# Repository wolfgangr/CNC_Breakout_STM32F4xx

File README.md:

## My Plan: build a Breakout Board for Blackpills

- [grbl-HAL STM32F4xx for blackpill_alt2 layout](https://github.com/grblHAL/STM32F4xx/blob/master/boards/blackpill_alt2_map.h)
- open collector drivers for all outputs
- screw connectors for high power stepper drivers and pins for smaller formats
- optocouplers for inputs
- control LED (optionally jumpered) for all in- and outputs
- jumpers on all Blackpill connectors, so that each pin can be rerouted independently
- 4 axes
- options for spindle encoders, VFD driver, THC analog input...
- wide input voltage range
- manufactured by JCBPCB or similiar

current projects in mind:
- routers/mills with auto-squared Y-axis
- lathe with spindle index for thread cutting
- plasma cutter with auto-squared Y-axis and torch height control

I selectet to fork Terje Io's project because of the kicad file format.

In the end, most of the hardware was closer to
https://github.com/phil-barrett/grblHAL-teensy-4.x
- simply because this design was closer to what I had in mind.

Please find updated information and discussion here at the github/grbl-HAL/core discussion area:
[STM324X1 blackpill experimental versatile GRBL-breakout board](https://github.com/grblHAL/core/discussions/562)

Project state as of July 2024:
- first batch arrived from the fab
- still yet untested

CAVEAT - DISCLAIMER:
Don't expect anything serious from the ideas, concepts and files delivered here.
Expect the worst, like your house set under fire, your machine going bust or whatever evil you may think of.

======== End of fork remarks ===========

## CNC Breakout board for Nucleo-64 based development boards using ST morpho extension header

[grblHAL driver](https://github.com/grblHAL/STM32F4xx) support for [Nucleo F411RE](https://www.st.com/en/evaluation-tools/nucleo-f411re.html) and [Nucleo F446RE](https://www.st.com/en/evaluation-tools/nucleo-f446re.html) development boards.

**NOTE:** design files are in [KiCad 5](http://www.kicad.org/) format!

**Features:**

* Four layer board

* 4-axis motor support with separate enable for all axes.

* On-board sockets for Polulu \(A4998 and DRV8825\) or Trinamic \(TMC2130 or TMC5160 - SPI mode, TMC2209 - UART mode\) style motor driver modules.

* Opto-coupled limit and signal inputs (X, Y, Z, A, Probe, Reset/E-Stop, Door, Feed Hold and Cycle Start).

* Opto-coupled signal outputs \(Spindle on, Spindle direction, Flood, Mist, Aux0 and Aux1\).
Outputs are open drain \(ULN2003\) capable of draining 500mA, enough to drive most relays directly.

* Jumper selectable drive voltage for inputs and outputs, either 5V internally supplied or 5-30V externally supplied. 
If externally supplied inputs and outputs can be made galvanically isolated from the controller via jumper settings.

* 5V buffered PWM output for spindle speed control.

* Optional optocoupled DC spindle output, can be made galvanically isolated via jumper setting. External supply voltage limited to rating of filtering capacitor C7 (max. 30V).

* I2C port with jumper selectable drive voltage \(3.3V or 5V\). This is complemented with a 5V tolerant input pin that may be used as an interrupt source, eg. for the strobe signal from a I2C-based keypad.

* Two GPIO ports, with two pins each. One is unbuffered and can be used for serial communincation, eg. for MPG or VFD control. One is input only and has 5V tolerant pins.

* Optional on-board EEPROM/FRAM for persistent storage of settings.

* SPI based SD-card interface. If not in use some or all pins may be used as GPIO or as a generic SPI interface with one chip select line, depending on motor drivers used.

---

I have a number of _bare_ boards available:

* 1.0 \(preliminary version\): 7 pcs. These do not support Trinamic drivers in SPI/UART mode and has a couple of correctable routing errors in the spindle PWM -> spindle DC circuit. Price: shipping at cost.

* 1.0b: 2 pcs. Price: EUR 5/pcs + shipping at cost. These are missing a pullup resistor for the keypad strobe input - this _may_ affect operation of the keypad plugin. Easy to add externally.

These boards are gold plated \(ENIG finish\).

* 1.0c: \(current version\) Not yet available.

I do not plan to offer populated boards as either I have to solder them myself \(will be expensive\) or place an order for ready made boards \(with only SMD components soldered\).  
A redesign is likely required for ready made boards as some of the components may not be available from the standard selection offered by e.g. [JLPCB](https://jlcpcb.com/).

It would be great if someone would get populated boards made and offered for sale as I am currently not prepared to do that.

---

2021-08-22

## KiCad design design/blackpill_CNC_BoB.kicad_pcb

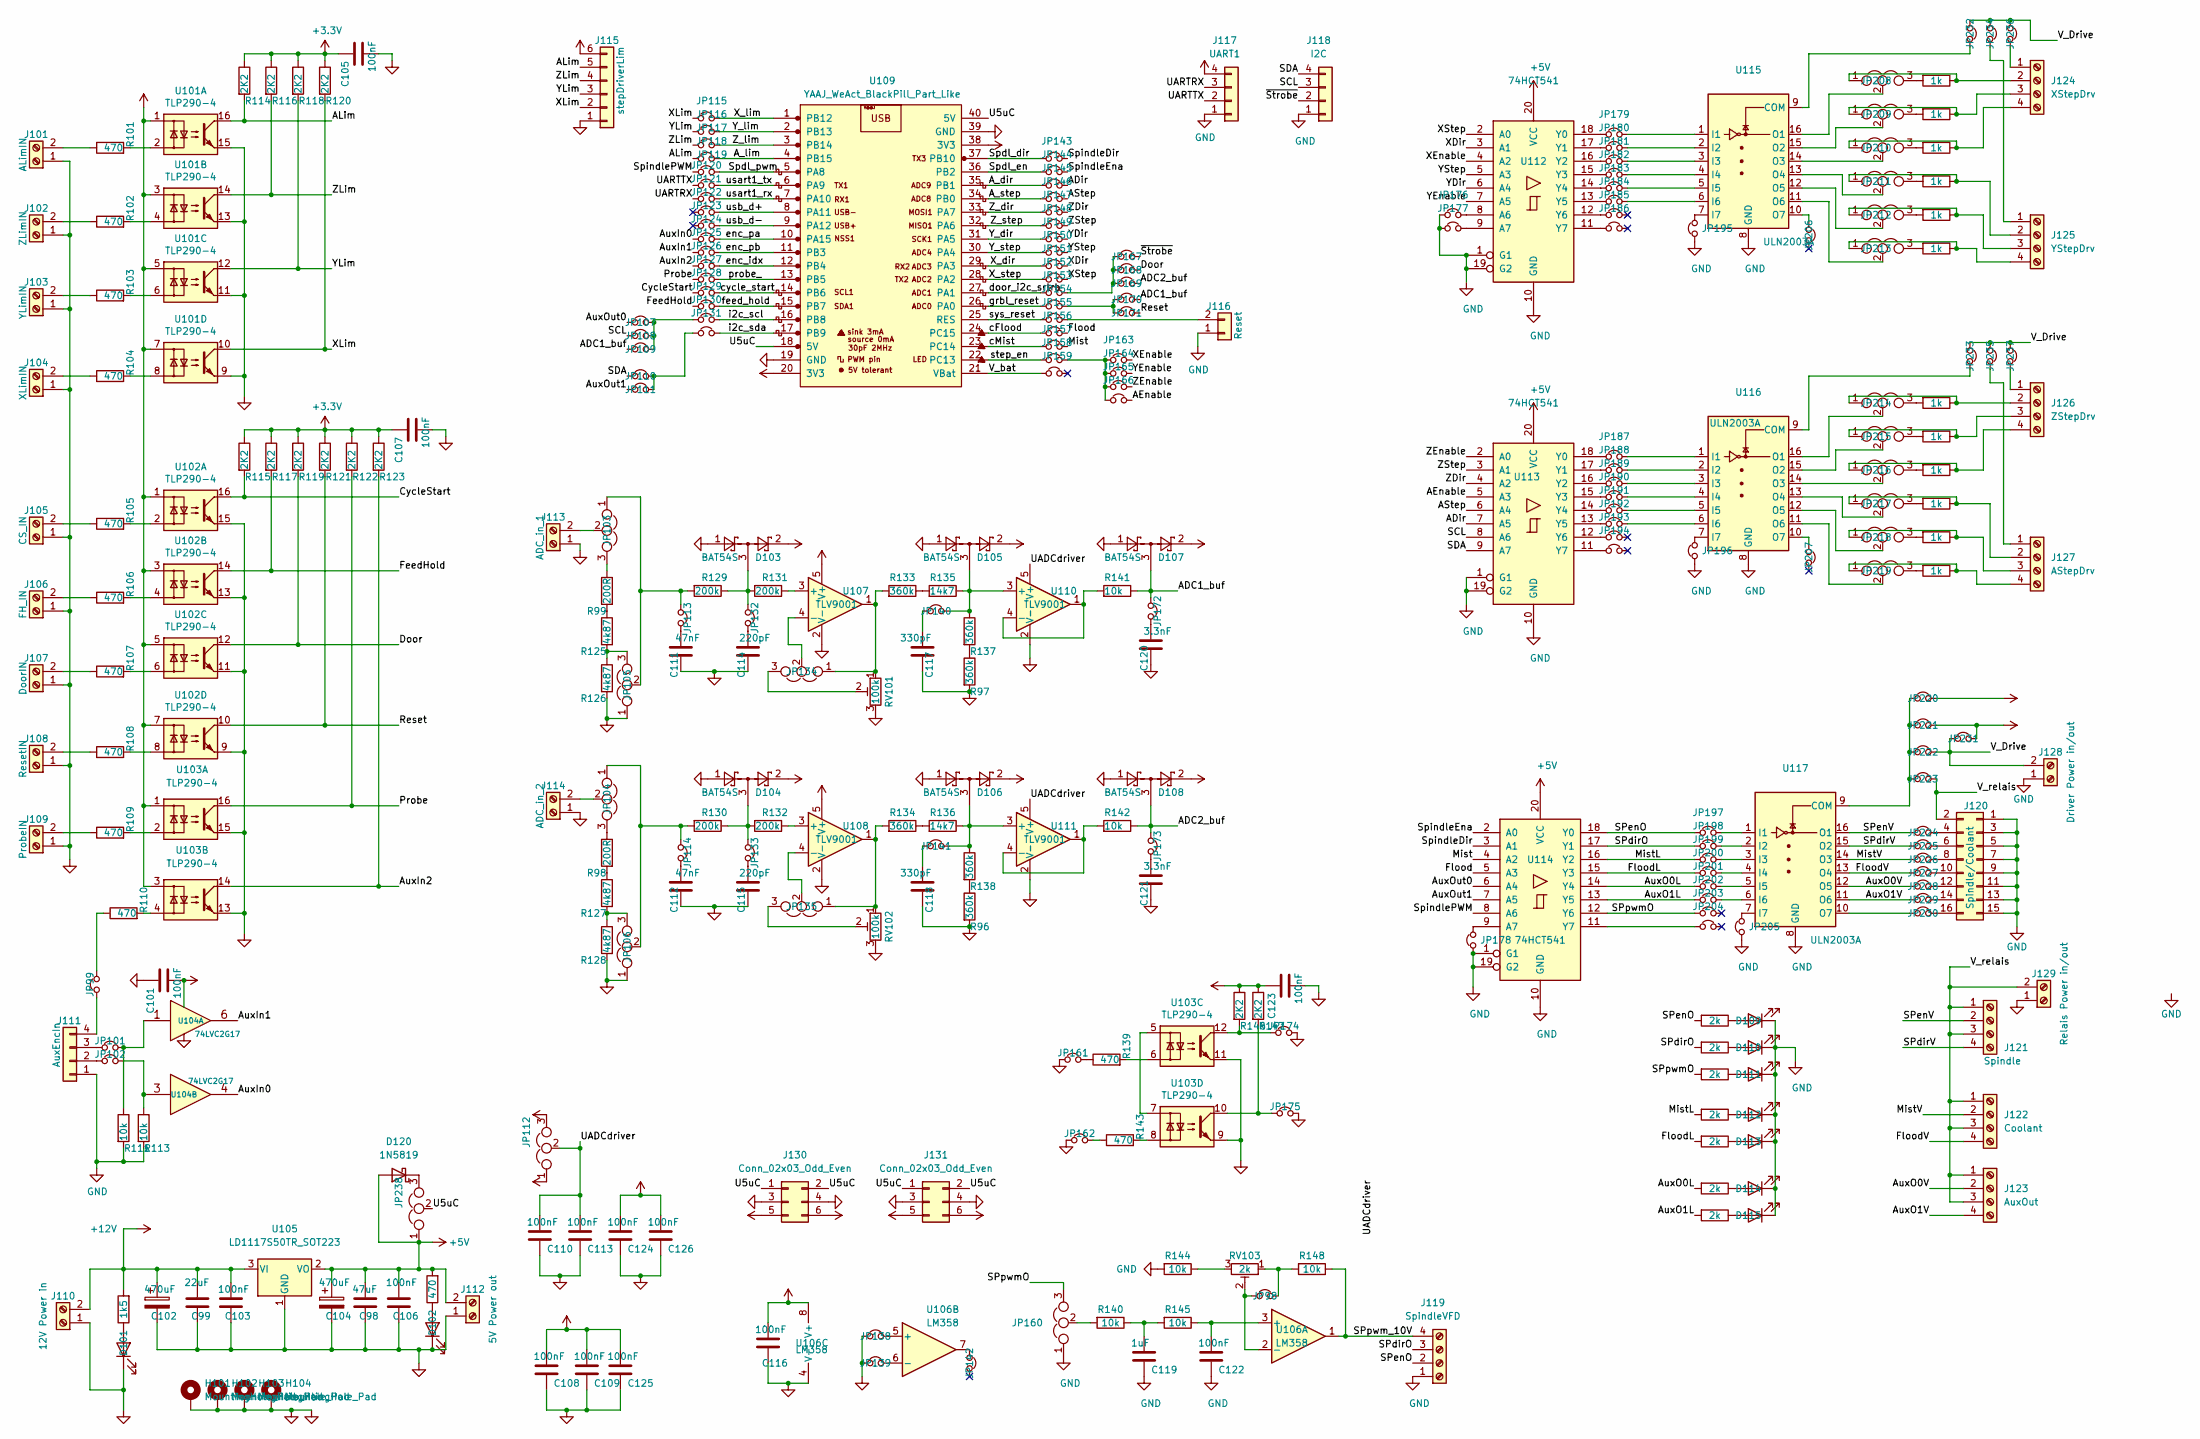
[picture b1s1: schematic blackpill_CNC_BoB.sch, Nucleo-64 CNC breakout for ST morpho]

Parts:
C98: 47uF; C_1206_3216Metric
C99: 22uF; C_1206_3216Metric
C101, C103, C105, C106, C107, C108, C109, C110, C113, C116, C122, C123, C124, C125, C126: 100nF; C_0603_1608Metric
C102, C104: 470uF; CP_Elec_10x10
C111, C112: 47nF; C_0603_1608Metric
C114, C115: 220pF; C_0402_1005Metric
C117, C118: 330pF; C_0603_1608Metric
C119: 1uF; C_0603_1608Metric
C120, C121: 3.3nF; C_0603_1608Metric
D101, D102: LED; LED_0805_2012Metric
D103, D104, D105, D106, D107, D108: BAT54S; SOT-23
D109, D110, D111, D112, D113, D114, D115: LED; LED_0603_1608Metric
D120: 1N5819; D_SOD-323
H101, H102, H103, H104: MountingHole_Pad; MountingHole_3.2mm_M3_Pad
J101: ALimIN; ScrewTerminal_1x2_P2.54mm_Vertical
J102: ZLimIN; ScrewTerminal_1x2_P2.54mm_Vertical
J103: YLimIN; ScrewTerminal_1x2_P2.54mm_Vertical
J104: XLimIN; ScrewTerminal_1x2_P2.54mm_Vertical
J105: CS_IN; ScrewTerminal_1x2_P2.54mm_Vertical
J106: FH_IN; ScrewTerminal_1x2_P2.54mm_Vertical
J107: DoorIN; ScrewTerminal_1x2_P2.54mm_Vertical
J108: ResetIN; ScrewTerminal_1x2_P2.54mm_Vertical
J109: ProbeIN; ScrewTerminal_1x2_P2.54mm_Vertical
J110: 12V Power in; PhoenixContact_MSTBA_2,5_2-G-5,08_1x02_P5.08mm_Horizontal
J111: AuxEncIn; PinSocket_1x04_P2.54mm_Vertical
J112: 5V Power out; ScrewTerminal_1x2_P2.54mm_Vertical
J113: ADC_in_1; ScrewTerminal_1x2_P2.54mm_Vertical
J114: ADC_in_2; ScrewTerminal_1x2_P2.54mm_Vertical
J115: stepDriverLim; PinSocket_1x06_P2.54mm_Vertical
J116: Reset; PinSocket_1x02_P2.54mm_Vertical
J117: UART1; PinSocket_1x04_P2.54mm_Vertical
J118: I2C; PinSocket_1x04_P2.54mm_Vertical
J119: SpindleVFD; ScrewTerminal_1x4_P2.54mm_Vertical
J120: Spindle/Coolant; PinSocket_2x08_P2.54mm_Vertical
J121: Spindle; ScrewTerminal_1x4_P2.54mm_Vertical
J122: Coolant; ScrewTerminal_1x4_P2.54mm_Vertical
J123: AuxOut; ScrewTerminal_1x4_P2.54mm_Vertical
J124: XStepDrv; ScrewTerminal_1x4_P2.54mm_Vertical
J125: YStepDrv; ScrewTerminal_1x4_P2.54mm_Vertical
J126: ZStepDrv; ScrewTerminal_1x4_P2.54mm_Vertical
J127: AStepDrv; ScrewTerminal_1x4_P2.54mm_Vertical
J128: Driver Power in/out; ScrewTerminal_1x2_P2.54mm_Vertical
J129: Relais Power in/out; ScrewTerminal_1x2_P2.54mm_Vertical
J130, J131: Conn_02x03_Odd_Even; PinHeader_2x03_P2.54mm_Vertical
JP98, JP99, JP101, JP102, JP107, JP108, JP109, JP110, JP111, JP113, JP114, JP115, JP116, JP117, JP118, JP119, JP120, JP121, JP122, JP123, JP124, JP125, JP126, JP127, JP128, JP129, JP130, JP131, JP132, JP133, JP138, JP139, JP140, JP141, JP142, JP143, JP144, JP145, JP146, JP147, JP148, JP149, JP150, JP151, JP152, JP153, JP154, JP155, JP156, JP157, JP158, JP159, JP161, JP162, JP163, JP164, JP165, JP166, JP167, JP168, JP169, JP170, JP171, JP172, JP173, JP174, JP175, JP176, JP177, JP178, JP179, JP180, JP181, JP182, JP183, JP184, JP185, JP186, JP187, JP188, JP189, JP190, JP191, JP192, JP193, JP194, JP195, JP196, JP197, JP198, JP199, JP200, JP201, JP202, JP203, JP204, JP205, JP206, JP207, JP220, JP221, JP222, JP223, JP224, JP225, JP226, JP227, JP228, JP229, JP230, JP231, JP232, JP233, JP234, JP235, JP236, JP237: Jumper_NC_Small; PinHeader_1x02_P2.54mm_Vertical
JP103, JP104, JP105, JP106, JP112, JP134, JP135, JP160, JP208, JP209, JP210, JP211, JP212, JP213, JP214, JP215, JP216, JP217, JP218, JP219, JP238: Jumper_NC_Dual; PinHeader_1x03_P2.54mm_Vertical
R96, R97, R133, R134, R137, R138: 360k; R_0603_1608Metric
R98, R99: 200R; R_0603_1608Metric
R101, R102, R103, R104, R105, R106, R107, R108, R109, R110, R124, R139, R143: 470; R_0805_2012Metric
R111, R113, R140, R141, R142, R144, R145, R148: 10k; R_0603_1608Metric
R112: 1k5; R_0805_2012Metric
R114, R115, R116, R117, R118, R119, R120, R121, R122, R123, R146, R147: 2K2; R_0603_1608Metric
R125, R126, R127, R128: 4k87; R_0805_2012Metric
R129, R130, R131, R132: 200k; R_0603_1608Metric
R135, R136: 14k7; R_0402_1005Metric
R149, R150, R151, R152, R153, R154, R167: 2k; R_0603_1608Metric
R155, R156, R157, R158, R159, R160, R161, R162, R163, R164, R165, R166: 1k; R_1206_3216Metric
RV101, RV102: 100k; Potentiometer_Bourns_3296W_Vertical
RV103: 2k; Potentiometer_Bourns_3296W_Vertical
U101, U102, U103: TLP290-4; SOP-16_4.4x10.4mm_P1.27mm
U104: 74LVC2G17; SOT-23-6
U105: LD1117S50TR_SOT223; SOT-223-3_TabPin2
U106: LM358; SOIC-8_3.9x4.9mm_P1.27mm
U107, U108, U110, U111: TLV9001; SOT-353_SC-70-5
U109: YAAJ_WeAct_BlackPill_Part_Like; YAAJ_WeAct_BlackPill_2
U112, U113, U114: 74HCT541; TSSOP-20_4.4x6.5mm_P0.65mm
U115, U116, U117: ULN2003A; SOIC-16_3.9x9.9mm_P1.27mm

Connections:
+5V: C98.1, C104.1, C106.1, C108.1, C109.1, C124.1, C125.1, C126.1, D103.2, D104.2, D120.2 (A), J112.2, J115.6, JP112.3, JP220.2, JP238.1, R124.2, U101.1, U101.3, U101.5, U101.7, U102.1, U102.3, U102.5, U102.7, U103.1, U103.3, U105.2 (VO), U107.5 (V+), U108.5 (V+), U112.20 (VCC), U113.20 (VCC), U114.20 (VCC)
+12V: C99.1, C102.1, C103.1, C116.1, J110.2, JP221.2, JP231.2, R112.2, U105.3 (VI), U106.8 (V+)
/ADC1_buf: D107.3, JP109.1, JP170.2, JP172.2, R141.1
/ADC2_buf: D108.3, JP169.2, JP173.2, R142.1
/ADir: JP145.2, U113.7 (A5)
/AEnable: JP166.2, U113.5 (A3)
/ALim: J115.5, JP118.1, R114.2, U101.16
/AStep: JP146.2, U113.6 (A4)
/A_dir: JP145.1, U109.35 (PB1)
/A_lim: JP118.2, U109.4 (PB15)
/A_step: JP146.1, U109.34 (PB0)
/AuxIn0: JP124.1, U104.4
/AuxIn1: JP125.1, U104.6
/AuxIn2: JP126.1, R123.2, U103.14
/AuxO0L: JP201.1, R154.2, U114.14 (Y4)
/AuxO0V: J123.2, JP228.1, U117.12 (O5)
/AuxO1L: JP202.1, R167.2, U114.13 (Y5)
/AuxO1V: J123.4, JP229.1, U117.11 (O6)
/AuxOut0: JP107.1, U114.6 (A4)
/AuxOut1: JP111.1, U114.7 (A5)
/CycleStart: JP128.1, R115.2, U102.16
/Door: JP168.2, R119.2, U102.12
/FeedHold: JP129.1, R117.2, U102.14
/Flood: JP156.2, U114.5 (A3)
/FloodL: JP200.1, R153.2, U114.15 (Y3)
/FloodV: J122.4, JP227.1, U117.13 (O4)
/Mist: JP157.2, U114.4 (A2)
/MistL: JP199.1, R152.2, U114.16 (Y2)
/MistV: J122.2, JP226.1, U117.14 (O3)
/Probe: JP127.1, R122.2, U103.16
/Reset: JP171.2, R121.2, U102.10
/SCL: J118.3, JP108.1, U113.8 (A6)
/SDA: J118.4, JP110.1, U113.9 (A7)
/SPdirO: J119.3, JP198.1, R150.2, U114.17 (Y1)
/SPdirV: J121.4, JP225.1, U117.15 (O2)
/SPenO: J119.2, JP197.1, R149.2, U114.18 (Y0)
/SPenV: J121.2, JP224.1, U117.16 (O1)
/SPpwmO: JP160.3, JP203.1, R151.2, U114.12 (Y6)
/SPpwm_10V: J119.4, R148.1, U106.1
/Spdl_dir: JP143.1, U109.37 (PB10)
/Spdl_en: JP144.1, U109.36 (PB2)
/Spdl_pwm: JP119.2, U109.5 (PA8)
/SpindleDir: JP143.2, U114.3 (A1)
/SpindleEna: JP144.2, U114.2 (A0)
/SpindlePWM: JP119.1, U114.8 (A6)
/U5uC: J130.1, J130.2, J131.1, J131.2, JP238.2, U109.18 (5V), U109.40 (5V)
/UADCdriver: C110.1, C113.1, JP112.2, U110.5 (V+), U111.5 (V+)
/UARTRX: J117.3, JP121.1
/UARTTX: J117.2, JP120.1
/V_Drive: J128.2, JP222.2, JP231.1, JP232.1, JP233.1, JP234.1, JP235.1, JP236.1, JP237.1
/V_bat: JP159.1, U109.21 (VBat)
/V_relais: J120.2, J121.1, J121.3, J122.1, J122.3, J123.1, J123.3, J129.2, JP223.2
/XDir: JP151.2, U112.3 (A1)
/XEnable: JP163.2, U112.4 (A2)
/XLim: J115.2, JP115.1, R120.2, U101.10
/XStep: JP152.2, U112.2 (A0)
/X_dir: JP151.1, U109.29 (PA3)
/X_lim: JP115.2, U109.1 (PB12)
/X_step: JP152.1, U109.28 (PA2)
/YDir: JP149.2, U112.6 (A4)
/YEnable: JP164.2, U112.7 (A5)
/YLim: J115.3, JP116.1, R118.2, U101.12
/YStep: JP150.2, U112.5 (A3)
/Y_dir: JP149.1, U109.31 (PA5)
/Y_lim: JP116.2, U109.2 (PB13)
/Y_step: JP150.1, U109.30 (PA4)
/ZDir: JP147.2, U113.4 (A2)
/ZEnable: JP165.2, U113.2 (A0)
/ZLim: J115.4, JP117.1, R116.2, U101.14
/ZStep: JP148.2, U113.3 (A1)
/Z_dir: JP147.1, U109.33 (PA7)
/Z_lim: JP117.2, U109.3 (PB14)
/Z_step: JP148.1, U109.32 (PA6)
/cFlood: JP156.1, U109.24 (PC15)
/cMist: JP157.1, U109.23 (PC14)
/cycle_start: JP128.2, U109.14 (PB6)
/door_i2c_srtrb: JP153.1, U109.27 (PA1)
/enc_idx: JP126.2, U109.12 (PB4)
/enc_pa: JP124.2, U109.10 (PA15)
/enc_pb: JP125.2, U109.11 (PB3)
/feed_hold: JP129.2, U109.15 (PB7)
/grbl_reset: JP154.1, U109.26 (PA0)
/i2c_scl: JP130.2, U109.16 (PB8)
/i2c_sda: JP131.2, U109.17 (PB9)
/probe_: JP127.2, U109.13 (PB5)
/step_en: JP158.1, U109.22 (PC13)
/sys_reset: JP155.1, U109.25 (RES)
/usart1_rx: JP121.2, U109.7 (PA10)
/usart1_tx: JP120.2, U109.6 (PA9)
/usb_d+: JP122.2, U109.8 (PA11)
/usb_d-: JP123.2, U109.9 (PA12)
/~Strobe: J118.2, JP167.2
GND: C98.2, C99.2, C101.2, C102.2, C103.2, C104.2, C105.1, C106.2, C107.1, C108.2, C109.2, C110.2, C111.2, C112.2, C113.2, C114.2, C115.2, C116.2, C117.2, C118.2, C119.2, C120.2, C121.2, C122.2, C123.1, C124.2, C125.2, C126.2, D101.1 (K), D102.1 (K), D103.1, D104.1, D105.1, D106.1, D107.1, D108.1, D109.1 (K), D110.1 (K), D111.1 (K), D112.1 (K), D113.1 (K), D114.1 (K), D115.1 (K), H101.1, H102.1, H103.1, H104.1, J101.1, J102.1, J103.1, J104.1, J105.1, J106.1, J107.1, J108.1, J109.1, J110.1, J111.1, J112.1, J113.1, J114.1, J115.1, J116.1, J117.1, J118.1, J119.1, J120.1, J120.3, J120.5, J120.7, J120.9, J120.11, J120.13, J120.15, J128.1, J129.1, J130.3, J130.4, J131.3, J131.4, JP105.1, JP106.1, JP138.1, JP139.1, JP160.1, JP161.2, JP162.2, JP174.1, JP175.1, JP176.1, JP177.1, JP178.1, JP195.1, JP196.1, JP205.1, R96.2, R97.2, R111.2, R113.2, R126.2, R128.2, R144.2, RV101.3, RV102.3, U101.9, U101.11, U101.13, U101.15, U102.9, U102.11, U102.13, U102.15, U103.9, U103.11, U103.13, U103.15, U104.2 (GND), U105.1 (GND), U106.4 (V-), U107.2 (V-), U108.2 (V-), U109.19 (GND), U109.39 (GND), U110.2 (V-), U111.2 (V-), U112.1 (G1), U112.10 (GND), U112.19 (G2), U113.1 (G1), U113.10 (GND), U113.19 (G2), U114.1 (G1), U114.10 (GND), U114.19 (G2), U115.8 (GND), U116.8 (GND), U117.8 (GND)
unnamed: C111.1, JP113.1
unnamed: C112.1, JP114.1
unnamed: C114.1, JP132.1
unnamed: C115.1, JP133.1
unnamed: C117.1, JP140.1
unnamed: C118.1, JP141.1
unnamed: C119.1, R140.1, R145.2
unnamed: C120.1, JP172.1
unnamed: C121.1, JP173.1
unnamed: C122.1, R145.1, U106.3 (+)
unnamed: D101.2 (A), R112.1
unnamed: D102.2 (A), R124.1
unnamed: D103.3, JP132.2, R129.1, R131.2
unnamed: D104.3, JP133.2, R130.1, R132.2
unnamed: D105.3, JP140.2, R135.1, R137.1, U110.3 (+)
unnamed: D106.3, JP141.2, R136.1, R138.1, U111.3 (+)
unnamed: D109.2 (A), R149.1
unnamed: D110.2 (A), R150.1
unnamed: D111.2 (A), R151.1
unnamed: D112.2 (A), R152.1
unnamed: D113.2 (A), R153.1
unnamed: D114.2 (A), R154.1
unnamed: D115.2 (A), R167.1
unnamed: D120.1 (K), JP238.3
unnamed: J101.2, R101.1
unnamed: J102.2, R102.1
unnamed: J103.2, R103.1
unnamed: J104.2, R104.1
unnamed: J105.2, R105.1
unnamed: J106.2, R106.1
unnamed: J107.2, R107.1
unnamed: J108.2, R108.1
unnamed: J109.2, R109.1
unnamed: J111.2, JP102.2
unnamed: J111.3, JP101.2
unnamed: J111.4, JP99.2
unnamed: J113.2, JP103.2
unnamed: J114.2, JP104.2
unnamed: J116.2, JP155.2
unnamed: J120.4, JP224.2
unnamed: J120.6, JP225.2
unnamed: J120.8, JP226.2
unnamed: J120.10, JP227.2
unnamed: J120.12, JP228.2
unnamed: J120.14, JP229.2
unnamed: J120.16, JP230.2
unnamed: J124.1, JP236.2
unnamed: J124.2, JP208.1, R155.1
unnamed: J124.3, JP209.1, R156.1
unnamed: J124.4, JP210.1, R157.1
unnamed: J125.1, JP234.2
unnamed: J125.2, JP211.1, R158.1
unnamed: J125.3, JP212.1, R159.1
unnamed: J125.4, JP213.1, R160.1
unnamed: J126.1, JP237.2
unnamed: J126.2, JP214.1, R161.1
unnamed: J126.3, JP215.1, R162.1
unnamed: J126.4, JP216.1, R163.1
unnamed: J127.1, JP235.2
unnamed: J127.2, JP217.1, R164.1
unnamed: J127.3, JP218.1, R165.1
unnamed: J127.4, JP219.1, R166.1
unnamed: JP98.1, RV103.2, U106.2 (-)
unnamed: JP98.2, R148.2, RV103.1
unnamed: JP99.1, R110.1
unnamed: JP101.1, R111.1, U104.1
unnamed: JP102.1, R113.1, U104.3
unnamed: JP103.1, JP105.2, JP113.2, R129.2
unnamed: JP103.3, R99.1
unnamed: JP104.1, JP106.2, JP114.2, R130.2
unnamed: JP104.3, R98.1
unnamed: JP105.3, R125.2, R126.1
unnamed: JP106.3, R127.2, R128.1
unnamed: JP107.2, JP108.2, JP109.2, JP130.1
unnamed: JP110.2, JP111.2, JP131.1
unnamed: JP134.1, R133.2, RV101.1, U107.1
unnamed: JP134.2, U107.4 (-)
unnamed: JP134.3, RV101.2
unnamed: JP135.1, R134.2, RV102.1, U108.1
unnamed: JP135.2, U108.4 (-)
unnamed: JP135.3, RV102.2
unnamed: JP138.2, U106.5 (+)
unnamed: JP139.2, U106.6 (-)
unnamed: JP142.1, U106.7
unnamed: JP153.2, JP167.1, JP168.1, JP169.1
unnamed: JP154.2, JP170.1, JP171.1
unnamed: JP158.2, JP163.1, JP164.1, JP165.1, JP166.1
unnamed: JP160.2, R140.2
unnamed: JP161.1, R139.1
unnamed: JP162.1, R143.1
unnamed: JP174.2, R146.2, U103.12
unnamed: JP175.2, R147.2, U103.10
unnamed: JP176.2, U112.8 (A6)
unnamed: JP177.2, U112.9 (A7)
unnamed: JP178.2, U114.9 (A7)
unnamed: JP179.1, U112.18 (Y0)
unnamed: JP179.2, U115.1 (I1)
unnamed: JP180.1, U112.17 (Y1)
unnamed: JP180.2, U115.2 (I2)
unnamed: JP181.1, U112.16 (Y2)
unnamed: JP181.2, U115.3 (I3)
unnamed: JP182.1, U112.15 (Y3)
unnamed: JP182.2, U115.4 (I4)
unnamed: JP183.1, U112.14 (Y4)
unnamed: JP183.2, U115.5 (I5)
unnamed: JP184.1, U112.13 (Y5)
unnamed: JP184.2, U115.6 (I6)
unnamed: JP185.1, U112.12 (Y6)
unnamed: JP186.1, U112.11 (Y7)
unnamed: JP187.1, U113.18 (Y0)
unnamed: JP187.2, U116.1 (I1)
unnamed: JP188.1, U113.17 (Y1)
unnamed: JP188.2, U116.2 (I2)
unnamed: JP189.1, U113.16 (Y2)
unnamed: JP189.2, U116.3 (I3)
unnamed: JP190.1, U113.15 (Y3)
unnamed: JP190.2, U116.4 (I4)
unnamed: JP191.1, U113.14 (Y4)
unnamed: JP191.2, U116.5 (I5)
unnamed: JP192.1, U113.13 (Y5)
unnamed: JP192.2, U116.6 (I6)
unnamed: JP193.1, U113.12 (Y6)
unnamed: JP194.1, U113.11 (Y7)
unnamed: JP195.2, U115.7 (I7)
unnamed: JP196.2, U116.7 (I7)
unnamed: JP197.2, U117.1 (I1)
unnamed: JP198.2, U117.2 (I2)
unnamed: JP199.2, U117.3 (I3)
unnamed: JP200.2, U117.4 (I4)
unnamed: JP201.2, U117.5 (I5)
unnamed: JP202.2, U117.6 (I6)
unnamed: JP204.1, U114.11 (Y7)
unnamed: JP205.2, U117.7 (I7)
unnamed: JP206.1, U115.10 (O7)
unnamed: JP207.1, U116.10 (O7)
unnamed: JP208.2, U115.16 (O1)
unnamed: JP208.3, R155.2
unnamed: JP209.2, U115.15 (O2)
unnamed: JP209.3, R156.2
unnamed: JP210.2, U115.14 (O3)
unnamed: JP210.3, R157.2
unnamed: JP211.2, U115.13 (O4)
unnamed: JP211.3, R158.2
unnamed: JP212.2, U115.12 (O5)
unnamed: JP212.3, R159.2
unnamed: JP213.2, U115.11 (O6)
unnamed: JP213.3, R160.2
unnamed: JP214.2, U116.16 (O1)
unnamed: JP214.3, R161.2
unnamed: JP215.2, U116.15 (O2)
unnamed: JP215.3, R162.2
unnamed: JP216.2, U116.14 (O3)
unnamed: JP216.3, R163.2
unnamed: JP217.2, U116.13 (O4)
unnamed: JP217.3, R164.2
unnamed: JP218.2, U116.12 (O5)
unnamed: JP218.3, R165.2
unnamed: JP219.2, U116.11 (O6)
unnamed: JP219.3, R166.2
unnamed: JP220.1, JP221.1, JP222.1, JP223.1, U117.9 (COM)
unnamed: JP230.1, U117.10 (O7)
unnamed: JP232.2, U115.9 (COM)
unnamed: JP233.2, U116.9 (COM)
unnamed: R101.2, U101.2
unnamed: R102.2, U101.4
unnamed: R103.2, U101.6
unnamed: R104.2, U101.8
unnamed: R105.2, U102.2
unnamed: R106.2, U102.4
unnamed: R107.2, U102.6
unnamed: R108.2, U102.8
unnamed: R109.2, U103.2
unnamed: R110.2, U103.4
unnamed: R99.2, R125.1
unnamed: R98.2, R127.1
unnamed: R131.1, U107.3 (+)
unnamed: R132.1, U108.3 (+)
unnamed: R133.1, R135.2
unnamed: R134.1, R136.2
unnamed: R97.1, R137.2
unnamed: R96.1, R138.2
unnamed: R139.2, U103.6
unnamed: R141.2, U110.1, U110.4 (-)
unnamed: R142.2, U111.1, U111.4 (-)
unnamed: R143.2, U103.8
unnamed: R144.1, RV103.3
unnamed: U103.5, U103.7

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
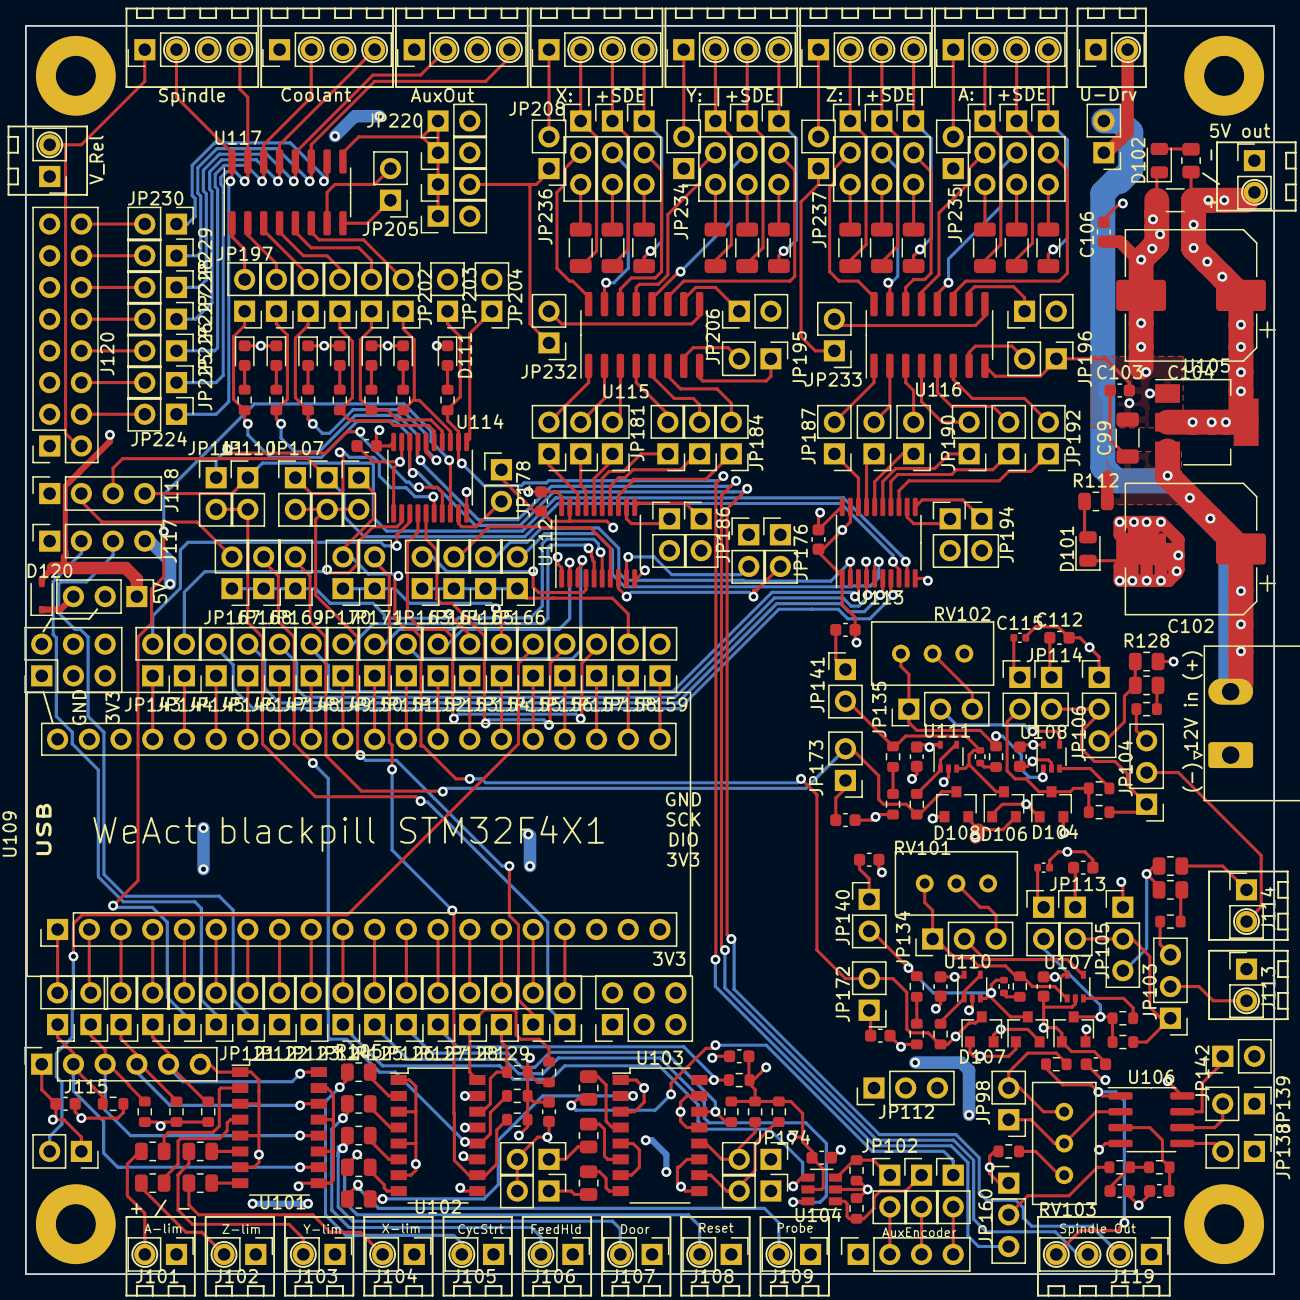
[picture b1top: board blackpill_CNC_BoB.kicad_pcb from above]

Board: 4 copper layers, 100.0 x 100.0 mm, 308 parts (0 on the bottom side), 281 nets.

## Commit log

2024-07-14 mark fork concept
2024-07-14 rescue parts not in standard lib
2024-07-14 add bluepill symbol and rename project
2024-07-14 get 3rd pty blackpill model
2024-07-14 add Black pill libs
2024-07-14 try to fix gitignore exceptions
2024-07-15 drafting jumper array
2024-07-15 drafted jumper array
2024-07-15 half of pin assignment
2024-07-15 roughly all of pin assignment
2024-07-15 rearrange output driver
2024-07-15 add bridgeable indicator LED
2024-07-15 complete w/o LED
2024-07-15 w/resistor and 3-pin jumper
2024-07-15 close to relais out stuff
2024-07-15 finished relais out stuff
2024-07-15 labelling out driver for transparency
2024-07-15 10V-lowpass-Analog spindle PWM
2024-07-15 reaarange input OC stuff
2024-07-15 2 mA low current LED
2024-07-15 power supply
2024-07-15 fine tuning...
2024-07-16 analog input buffer
2024-07-17 redraft, before annotation reorder
2024-07-17 after annotation reorder
2024-07-17 redraft adc in after spicing
2024-07-17 add connectivity to loose ends
2024-07-17 checkd, try to cont workflow
2024-07-18 git cleanup
2024-07-18 JLBPCB tuned capacitors
2024-07-18 JLBPCB tuned resistors
2024-07-18 rework footprints
2024-07-18 rework BOM and correct quite some errors
2024-07-18 start routing pcb
2024-07-18 placed jp along µc
2024-07-18 presorting output rail
2024-07-18 presorting digi input and power
2024-07-18 arranging pwm output
2024-07-18 arranging PWM DAC output
2024-07-18 updated J111 correction
2024-07-18 arranging decoder input circuitry
2024-07-19 add schottky to blackpill 5V
2024-07-19 change screw terminals and start placing analog in
2024-07-19 place buffer cercos
2024-07-19 refigure AD in jumper
2024-07-19 refigure driver voltage jumper
2024-07-19 still ... refigure driver voltage jumper
2024-07-19 arrange adc in
2024-07-19 align top edge connectors
2024-07-19 arranged output lines
2024-07-19 start placing controller
2024-07-19 added exp power pins
2024-07-19 placed optocouplers
2024-07-19 placed aux in
2024-07-19 placed power
2024-07-19 placed mount holes
2024-07-19 rearrange top left
2024-07-19 rearrange bottom left
2024-07-19 rearrange aux in
2024-07-19 clear space bottom right
2024-07-19 place pwm output
2024-07-19 ignore *.tgz
2024-07-19 define board size
2024-07-20 lock all jumpers and connectors
2024-07-20 add 3.3 and 5V planes
2024-07-20 routing...
2024-07-20 routed front as possible...
2024-07-20 starte routing backside
2024-07-20 simple stuff done
2024-07-20 routing diff power
2024-07-20 routing bot right
2024-07-20 tuning power plates
2024-07-20 routing hard stuff
2024-07-20 routed hard stuff
2024-07-20 test runs - so far ok
2024-07-21 fixing JCLPCB warnings
2024-07-21 finished changing jclpcb warnings
2024-07-21 DRC check after changes OK
2024-07-21 fixed power seq error at bluepill
2024-07-31 cleanup after PCB ordering
2024-07-31 png copies of media pdf
2024-08-01 add picture
2024-08-01 rescale image

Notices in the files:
design/blackpill_CNC_BoB.sch:
Licensed under CERN OHL v.1.2 or later
